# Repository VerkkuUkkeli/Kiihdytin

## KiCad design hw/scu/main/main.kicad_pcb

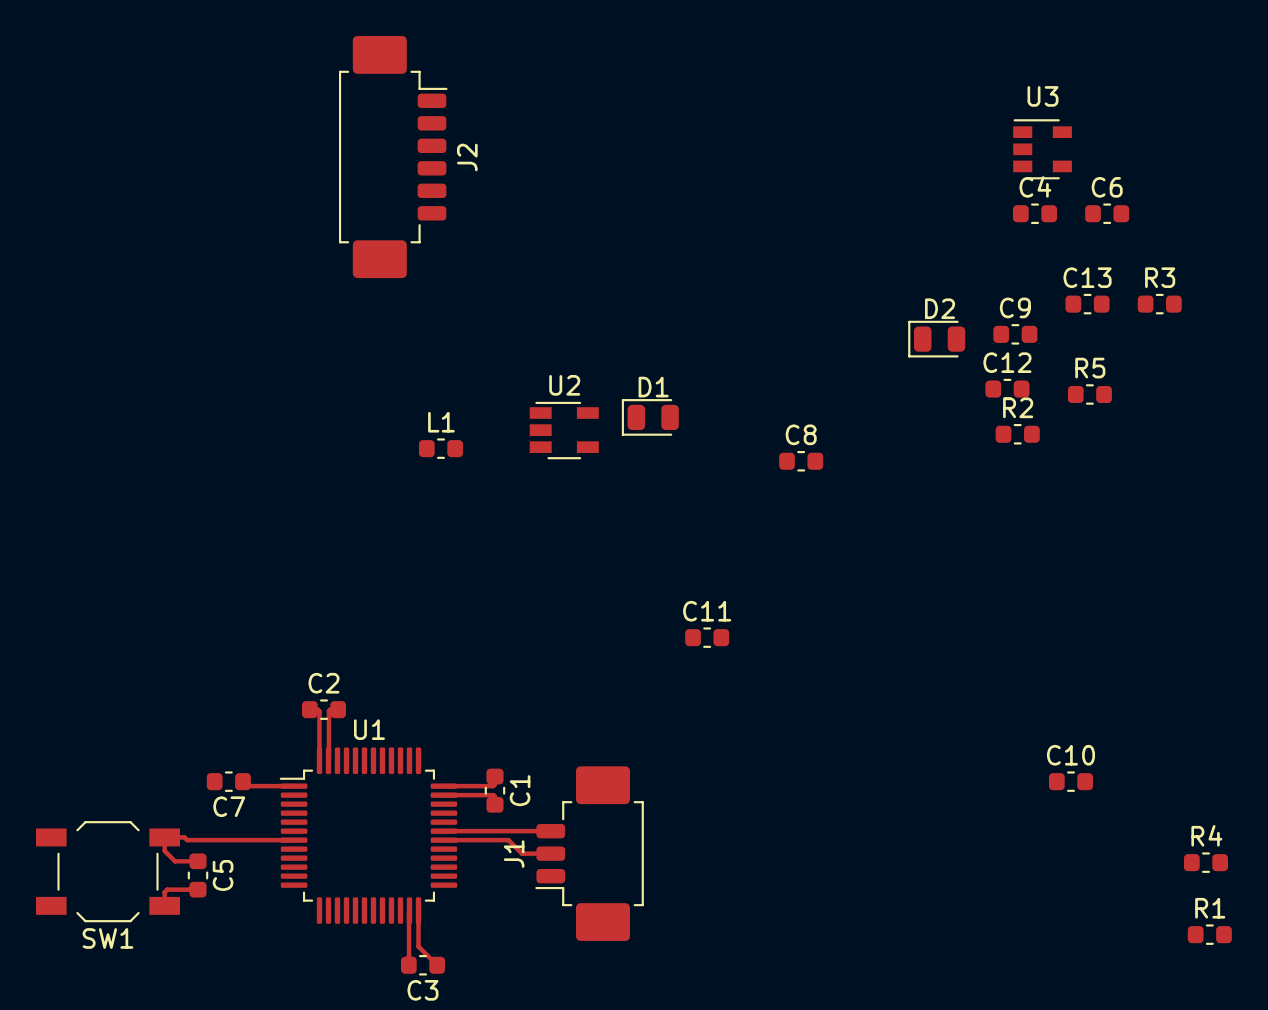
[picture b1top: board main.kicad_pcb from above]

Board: 2 copper layers, 27 parts (0 on the bottom side), 16 nets.

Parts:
C1, C2, C3, C5, C7: 100n; C_0603_1608Metric
C4, C9, C11: 4.7u; C_0603_1608Metric
C6: 10n; C_0603_1608Metric
C8, C10, C12: 1u; C_0603_1608Metric
C13: 10u; C_0603_1608Metric
D1, D2: LED; LED_0805_2012Metric
J1: Conn_01x03_MountingPin; Molex_PicoBlade_53261-0371_1x03-1MP_P1.25mm_Horizontal
J2: Conn_01x06_MountingPin; Molex_PicoBlade_53261-0671_1x06-1MP_P1.25mm_Horizontal
L1: 10u; L_0603_1608Metric
R1, R2, R3, R4: 10k; R_0603_1608Metric
R5: 470k; R_0603_1608Metric
SW1: SW_Push; SW_SPST_TL3342
U1: STM32F072C8Tx; LQFP-48_7x7mm_P0.5mm
U2: LM3670MF; TSOT-23-5
U3: LP5907MFX-3.3; SOT-23-5

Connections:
/3V3_A: C6.1, C8.1, C12.1, U1.9, U3.5
/3V3_D: C1.1, C2.1, C3.1, C4.1, C7.1, C9.1, C13.1, J2.1, L1.2, R4.2, U1.1, U1.24, U1.36, U1.48, U2.4
/LED_1: D1.2, U1.27
/LED_2: D2.2, U1.28
/NRST: C5.1, J2.5, SW1.2, U1.7
/SWCLK: J2.2, U1.37
/SWDIO: J2.4, U1.34
/USART1_RX: J1.3, U1.31
/USART1_TX: J1.2, U1.30
/V_USB: C10.1, C11.1, R5.1, U2.1, U2.3, U3.1
GND: C1.2, C2.2, C3.2, C4.2, C5.2, C6.2, C7.2, C8.2, C9.2, C10.2, C11.2, C12.2, C13.2, J1.1, J1.MP, J2.3, J2.MP, R1.2, R2.1, R3.1, SW1.1, U1.8, U1.23, U1.35, U1.47, U2.2, U3.2
unnamed: D1.1, R2.2
unnamed: D2.1, R3.2
unnamed: L1.1, U2.5
unnamed: R1.1, R4.1, U1.44
unnamed: R5.2, U3.3

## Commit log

2019-11-04 Create initial directory structure
2019-11-04 Init hardware development branch
2019-12-18 Start adding STM32F072 reference design schematic.
2019-12-21 Add HSE crystal
2021-01-18 Add electromagnet driver schematics
2021-01-31 Finish laying out relelauta v2.0 PCB. Minor tweaks to motherboard.
2021-01-31 Add missing silkscreen markings
2021-01-31 Board layouts before checking gerbers for alignment
